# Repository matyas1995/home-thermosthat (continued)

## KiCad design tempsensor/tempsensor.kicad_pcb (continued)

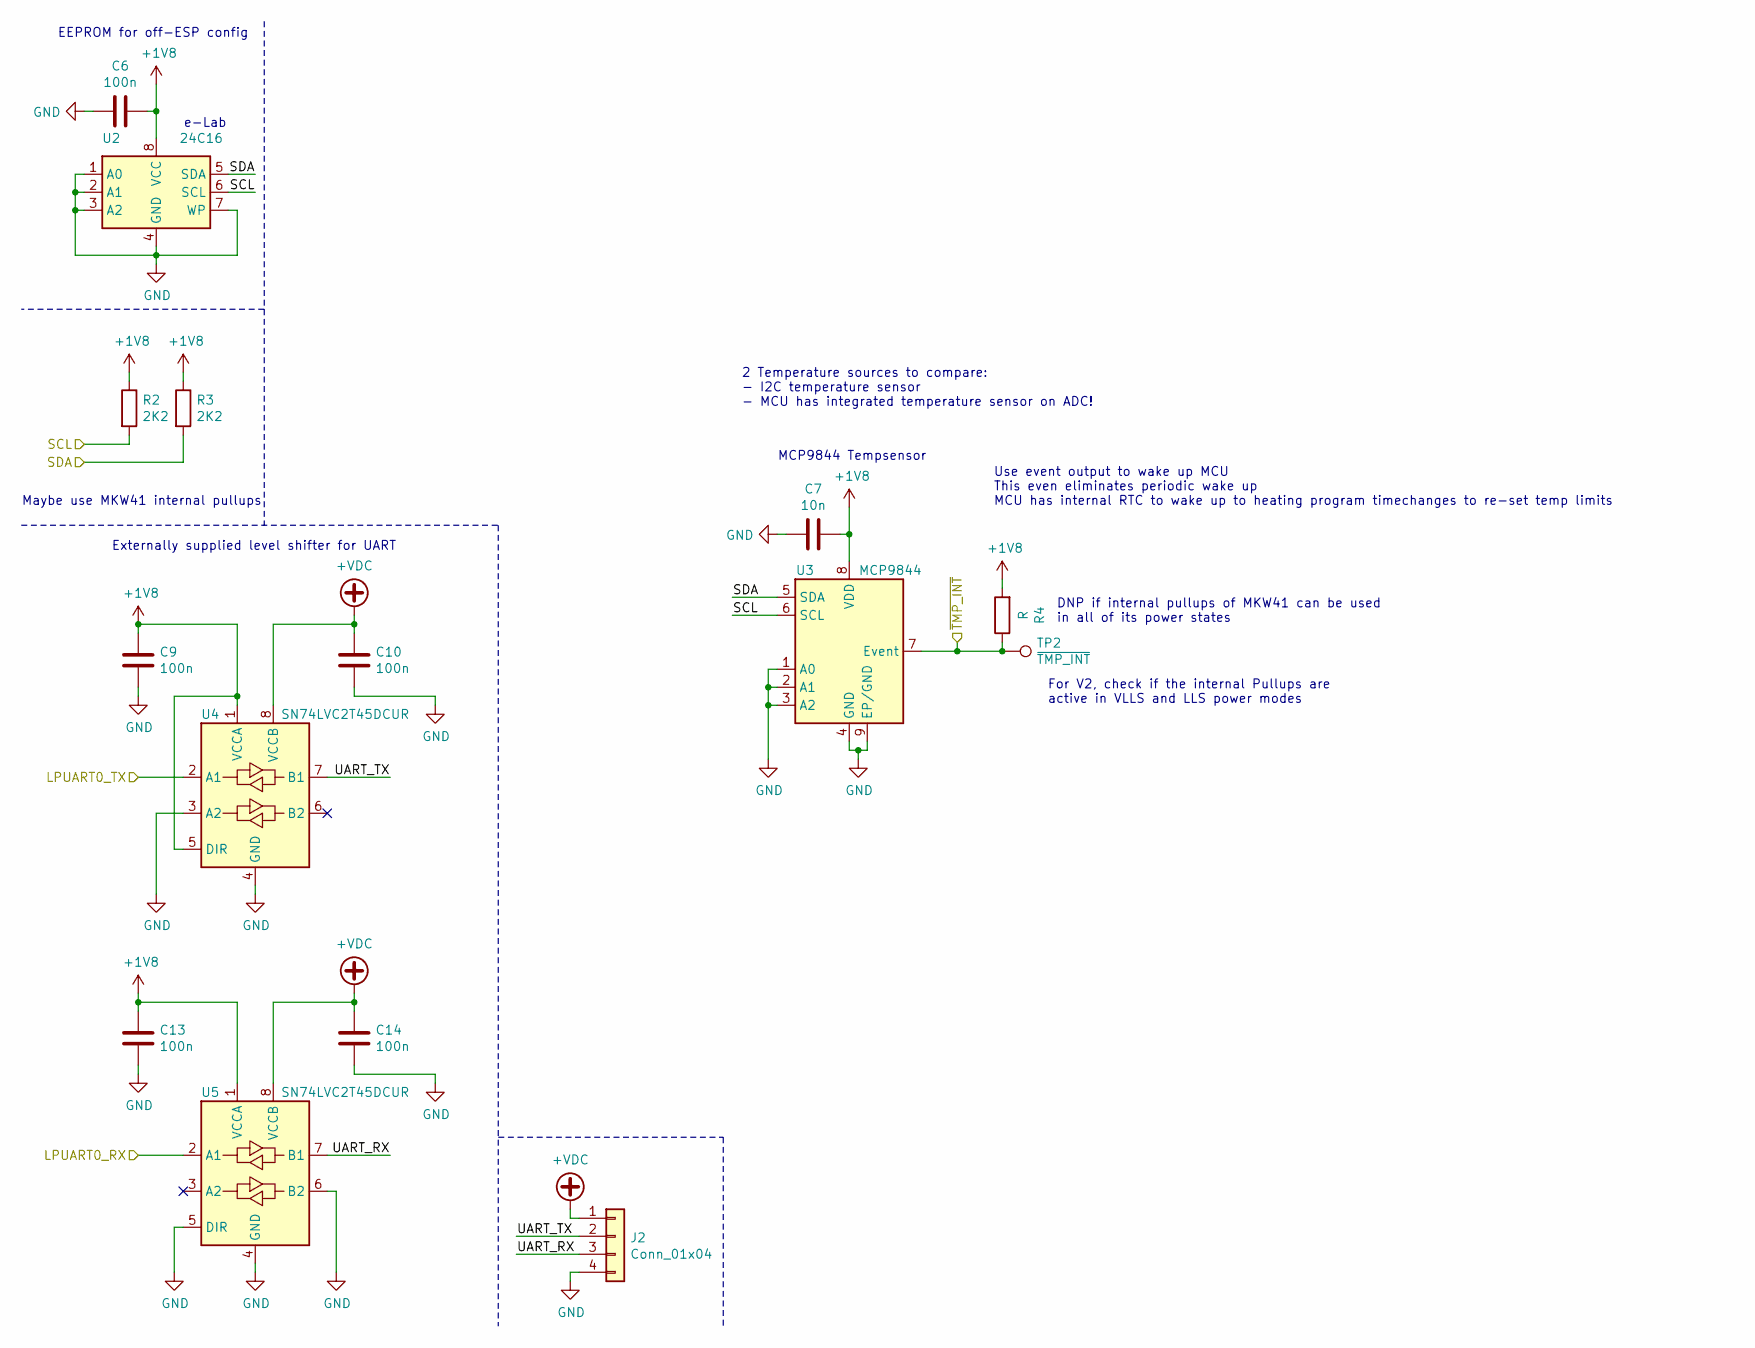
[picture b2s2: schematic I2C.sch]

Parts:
C6: 100n; C_0603_1608Metric
C7: 10n; C_0603_1608Metric
C9, C10, C13, C14: 100n; C_0402_1005Metric
J2: Conn_01x04; PinHeader_2x02_P2.54mm_Vertical
R2, R3: 2K2; R_0603_1608Metric
R4: R; R_0402_1005Metric
TP2: ~TMP_INT; TestPoint_Pad_D1.0mm
U2: 24C16; SOIC-8_3.9x4.9mm_P1.27mm
U3: MCP9844; DFN-8-1EP_3x2mm_P0.5mm_EP1.36x1.46mm
U4, U5: SN74LVC2T45DCUR; VSSOP-8_2.4x2.1mm_P0.5mm

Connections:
+1V8: C6.1, C7.1, C9.1, C13.1, R2.1, R3.1, R4.2, U2.8 (VCC), U3.8 (VDD), U4.1 (VCCA), U4.5 (DIR), U5.1 (VCCA); also elsewhere on the board
+VDC: C10.1, C14.1, J2.1, U4.8 (VCCB), U5.8 (VCCB)
/I2C/UART_RX: J2.3, U5.7 (B1)
/I2C/UART_TX: J2.2, U4.7 (B1)
/LPUART0_RX: U5.2 (A1); also elsewhere on the board
/LPUART0_TX: U4.2 (A1); also elsewhere on the board
/SCL: R2.2, U2.6 (SCL), U3.6 (SCL); also elsewhere on the board
/SDA: R3.2, U2.5 (SDA), U3.5 (SDA); also elsewhere on the board
/~TMP_INT: R4.1, TP2.1, U3.7 (Event); also elsewhere on the board
GND: C6.2, C7.2, C9.2, C10.2, C13.2, C14.2, J2.4, U2.1 (A0), U2.2 (A1), U2.3 (A2), U2.4 (GND), U2.7 (WP), U3.1 (A0), U3.2 (A1), U3.3 (A2), U3.4 (GND), U3.9 (EP/GND), U4.3 (A2), U4.4 (GND), U5.4 (GND), U5.5 (DIR), U5.6 (B2); also elsewhere on the board

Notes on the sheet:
EEPROM for off-ESP config
e-Lab
MCP9844 Tempsensor
Use event output to wake up MCU This even eliminates periodic wake up MCU has internal RTC to wake up to heating program timechanges to re-set temp limits
DNP if internal pullups of MKW41 can be used in all of its power states
For V2, check if the internal Pullups are active in VLLS and LLS power modes
Externally supplied level shifter for UART
Maybe use MKW41 internal pullups
2 Temperature sources to compare: - I2C temperature sensor - MCU has integrated temperature sensor on ADC!

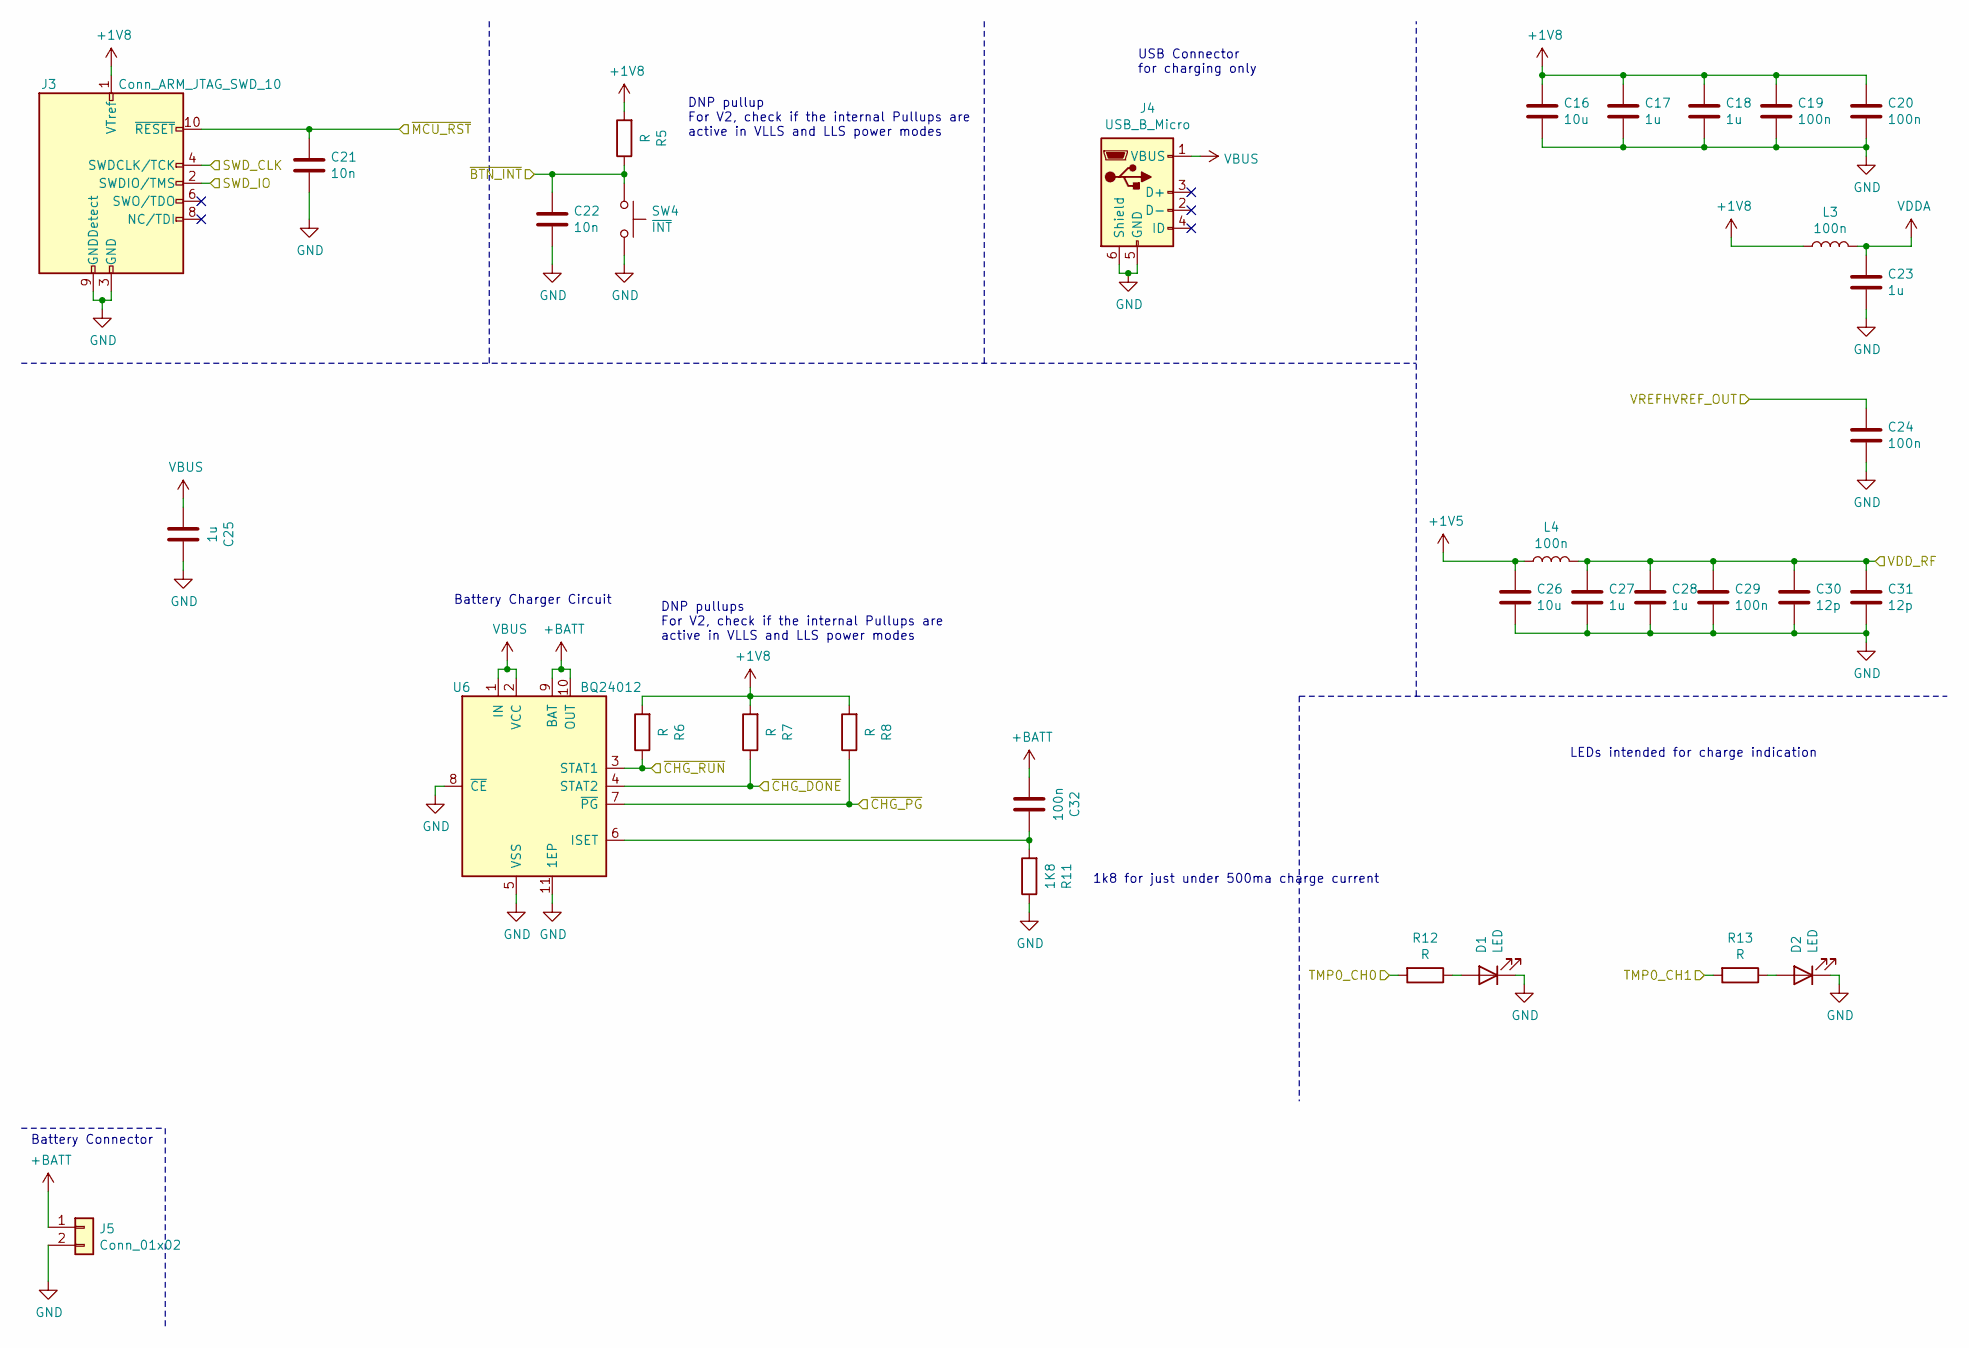
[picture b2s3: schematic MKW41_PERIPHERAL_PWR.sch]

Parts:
C16, C26: 10u; C_0603_1608Metric
C17, C18, C23, C27, C28: 1u; C_0402_1005Metric
C19, C20, C24, C29, C32: 100n; C_0402_1005Metric
C21, C22: 10n; C_0402_1005Metric
C25: 1u; C_0603_1608Metric
C30, C31: 12p; C_0402_1005Metric
D1, D2: LED; LED_0603_1608Metric
J3: Conn_ARM_JTAG_SWD_10; PinHeader_2x05_P1.27mm_Vertical_SMD
J4: USB_B_Micro; USB-Mini-B_Wuerth_651005136521_Horizontal
J5: Conn_01x02; PinHeader_1x02_P2.54mm_Vertical
L3, L4: 100n; L_0402_1005Metric
R5, R12, R13: R; R_0603_1608Metric
R6, R7, R8: R; R_0402_1005Metric
R11: 1K8; R_0402_1005Metric
SW4: ~INT; SW_PUSH_6mm_H5mm
U6: BQ24012; VSON-10-1EP_3x3mm_P0.5mm_EP1.65x2.4mm_ThermalVias

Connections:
+1V5: C26.1, L4.1; also elsewhere on the board
+1V8: C16.1, C17.1, C18.1, C19.1, C20.1, J3.1 (VTref), L3.1, R5.2, R6.2, R7.2, R8.2; also elsewhere on the board
+BATT: C32.2, J5.1, U6.9 (BAT), U6.10 (OUT); also elsewhere on the board
/SWD_CLK: J3.4 (SWDCLK/TCK); also elsewhere on the board
/SWD_IO: J3.2 (SWDIO/TMS); also elsewhere on the board
/TMP0_CH0: R12.2; also elsewhere on the board
/TMP0_CH1: R13.2; also elsewhere on the board
/VDD_RF: C27.1, C28.1, C29.1, C30.1, C31.1, L4.2; also elsewhere on the board
/VREFHVREF_OUT: C24.1; also elsewhere on the board
/~BTN_INT: C22.1, R5.1, SW4.1; also elsewhere on the board
/~CHG_DONE: R7.1, U6.4 (STAT2); also elsewhere on the board
/~CHG_PG: R8.1, U6.7 (~PG); also elsewhere on the board
/~CHG_RUN: R6.1, U6.3 (STAT1); also elsewhere on the board
/~MCU_RST: C21.1, J3.10 (~RESET~); also elsewhere on the board
GND: C16.2, C17.2, C18.2, C19.2, C20.2, C21.2, C22.2, C23.2, C24.2, C25.1, C26.2, C27.2, C28.2, C29.2, C30.2, C31.2, D1.1 (K), D2.1 (K), J3.3 (GND), J3.5 (GND), J3.9 (GNDDetect), J4.5 (GND), J4.6 (Shield), J5.2, R11.1, SW4.2, U6.5 (VSS), U6.8 (~CE), U6.11 (1EP); also elsewhere on the board
unnamed: C32.1, R11.2, U6.6 (ISET)
unnamed: D1.2 (A), R12.1
unnamed: D2.2 (A), R13.1
VBUS: C25.2, J4.1 (VBUS), U6.1 (IN), U6.2 (VCC)
VDDA: C23.1, L3.2; also elsewhere on the board

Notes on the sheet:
DNP pullup For V2, check if the internal Pullups are active in VLLS and LLS power modes
Battery Connector
Battery Charger Circuit
USB Connector for charging only
DNP pullups For V2, check if the internal Pullups are active in VLLS and LLS power modes
LEDs intended for charge indication
1k8 for just under 500ma charge current

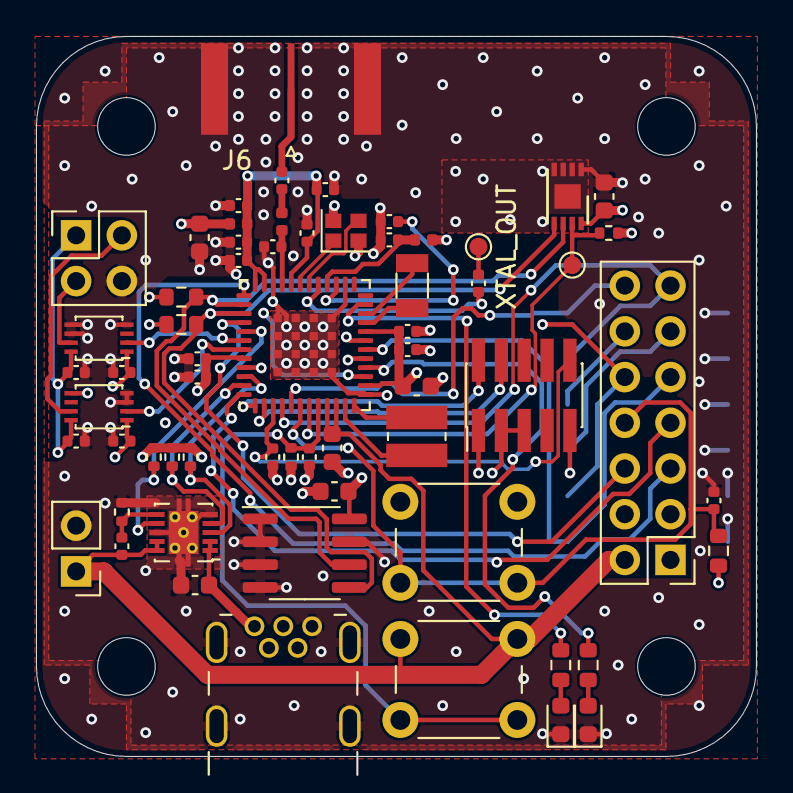
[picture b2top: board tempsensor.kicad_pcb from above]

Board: 4 copper layers, 40.0 x 40.0 mm, 64 parts (1 on the bottom side), 49 nets.

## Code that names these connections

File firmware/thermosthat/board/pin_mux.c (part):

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mcu_data: ksdk2_0
processor_version: 10.0.0
pin_labels:
- {pin_num: '16', pin_signal: PTB0/LLWU_P8/XTAL_OUT_EN/I2C0_SCL/CMP0_OUT/TPM0_CH1/CLKOUT, label: LED_YELLOW, identifier: LED_YELLOW}
- {pin_num: '17', pin_signal: ADC0_SE1/CMP0_IN5/PTB1/DTM_RX/I2C0_SDA/LPTMR0_ALT1/TPM0_CH2/CMT_IRO, label: LED_RED, identifier: LED_RED}
- {pin_num: '23', pin_signal: DAC0_OUT/ADC0_SE4/CMP0_IN2/PTB18/I2C1_SCL/TPM_CLKIN0/TPM0_CH0/NMI_b, label: REG_OUT, identifier: REG_OUT}
- {pin_num: '41', pin_signal: TSI0_CH1/PTC5/LLWU_P13/RF_NOT_ALLOWED/LPTMR0_ALT2/UART0_RTS_b/TPM1_CH1/BSM_CLK, label: BTN_INT, identifier: BTN_INT}
- {pin_num: '45', pin_signal: TSI0_CH4/PTC16/LLWU_P0/SPI0_SCK/I2C0_SDA/UART0_RTS_b/TPM0_CH3, label: LED_GREEN, identifier: LED_GREEN}
- {pin_num: '46', pin_signal: TSI0_CH5/PTC17/LLWU_P1/SPI0_SOUT/I2C1_SCL/UART0_RX/BSM_FRAME/DTM_RX, label: BTN_OK, identifier: BTN_OK}
- {pin_num: '47', pin_signal: TSI0_CH6/PTC18/LLWU_P2/SPI0_SIN/I2C1_SDA/UART0_TX/BSM_DATA/DTM_TX, label: DP_RST, identifier: DP_RST}
- {pin_num: '48', pin_signal: TSI0_CH7/PTC19/LLWU_P3/SPI0_PCS0/I2C0_SCL/UART0_CTS_b/BSM_CLK/BLE_RF_ACTIVE, label: DP_BUSY, identifier: DP_BUSY}
 * BE CAREFUL MODIFYING THIS COMMENT - IT IS YAML SETTINGS FOR TOOLS ***********
 */
/* clang-format on */
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BOARD_InitPins:
- options: {callFromInitBoot: 'true', coreID: core0, enableClock: 'true'}
- pin_list:
  - {pin_num: '4', peripheral: SPI1, signal: SOUT, pin_signal: TSI0_CH10/PTA16/LLWU_P4/SPI1_SOUT/TPM0_CH0}
  - {pin_num: '6', peripheral: SPI1, signal: SCK, pin_signal: TSI0_CH12/PTA18/LLWU_P6/SPI1_SCK/TPM2_CH0}
  - {pin_num: '7', peripheral: SPI1, signal: PCS0_SS, pin_signal: TSI0_CH13/ADC0_SE5/PTA19/LLWU_P7/SPI1_PCS0/TPM2_CH1}
  - {pin_num: '16', peripheral: GPIOB, signal: 'GPIO, 0', pin_signal: PTB0/LLWU_P8/XTAL_OUT_EN/I2C0_SCL/CMP0_OUT/TPM0_CH1/CLKOUT, direction: OUTPUT}
  - {pin_num: '17', peripheral: GPIOB, signal: 'GPIO, 1', pin_signal: ADC0_SE1/CMP0_IN5/PTB1/DTM_RX/I2C0_SDA/LPTMR0_ALT1/TPM0_CH2/CMT_IRO, direction: OUTPUT}
  - {pin_num: '21', peripheral: RTC, signal: EXTAL32K, pin_signal: EXTAL32K/PTB16/I2C1_SCL/TPM2_CH0}
  - {pin_num: '22', peripheral: RTC, signal: XTAL32K, pin_signal: XTAL32K/PTB17/I2C1_SDA/TPM2_CH1/BSM_CLK}
  - {pin_num: '23', peripheral: GPIOB, signal: 'GPIO, 18', pin_signal: DAC0_OUT/ADC0_SE4/CMP0_IN2/PTB18/I2C1_SCL/TPM_CLKIN0/TPM0_CH0/NMI_b, direction: OUTPUT}
  - {pin_num: '38', peripheral: I2C1, signal: CLK, pin_signal: TSI0_CH14/PTC2/LLWU_P10/TX_SWITCH/I2C1_SCL/UART0_RX/CMT_IRO/DTM_RX}
  - {pin_num: '39', peripheral: I2C1, signal: SDA, pin_signal: TSI0_CH15/PTC3/LLWU_P11/RX_SWITCH/I2C1_SDA/UART0_TX/TPM0_CH1/DTM_TX}
  - {pin_num: '41', peripheral: GPIOC, signal: 'GPIO, 5', pin_signal: TSI0_CH1/PTC5/LLWU_P13/RF_NOT_ALLOWED/LPTMR0_ALT2/UART0_RTS_b/TPM1_CH1/BSM_CLK, direction: INPUT}
  - {pin_num: '45', peripheral: GPIOC, signal: 'GPIO, 16', pin_signal: TSI0_CH4/PTC16/LLWU_P0/SPI0_SCK/I2C0_SDA/UART0_RTS_b/TPM0_CH3, direction: OUTPUT, gpio_init_state: 'true'}
  - {pin_num: '46', peripheral: GPIOC, signal: 'GPIO, 17', pin_signal: TSI0_CH5/PTC17/LLWU_P1/SPI0_SOUT/I2C1_SCL/UART0_RX/BSM_FRAME/DTM_RX, direction: INPUT}
  - {pin_num: '47', peripheral: GPIOC, signal: 'GPIO, 18', pin_signal: TSI0_CH6/PTC18/LLWU_P2/SPI0_SIN/I2C1_SDA/UART0_TX/BSM_DATA/DTM_TX, direction: OUTPUT}
  - {pin_num: '48', peripheral: GPIOC, signal: 'GPIO, 19', pin_signal: TSI0_CH7/PTC19/LLWU_P3/SPI0_PCS0/I2C0_SCL/UART0_CTS_b/BSM_CLK/BLE_RF_ACTIVE, direction: INPUT}
  - {pin_num: '43', peripheral: LPUART0, signal: TX, pin_signal: TSI0_CH3/PTC7/LLWU_P15/SPI0_PCS2/I2C1_SDA/UART0_TX/TPM2_CH1/BSM_DATA}
  - {pin_num: '42', peripheral: LPUART0, signal: RX, pin_signal: TSI0_CH2/PTC6/LLWU_P14/XTAL_OUT_EN/I2C1_SCL/UART0_RX/TPM2_CH0/BSM_FRAME}
 * BE CAREFUL MODIFYING THIS COMMENT - IT IS YAML SETTINGS FOR TOOLS ***********
 */
/* clang-format on */
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        .pinDirection = kGPIO_DigitalInput,
        .outputLogic = 0U
    };
    /* Initialize GPIO functionality on pin PTC19 (pin 48)  */
    GPIO_PinInit(BOARD_INITPINS_DP_BUSY_GPIO, BOARD_INITPINS_DP_BUSY_PIN, &DP_BUSY_config);

    /* PORTA16 (pin 4) is configured as SPI1_SOUT */
    PORT_SetPinMux(PORTA, 16U, kPORT_MuxAlt2);

    /* PORTA18 (pin 6) is configured as SPI1_SCK */
    PORT_SetPinMux(PORTA, 18U, kPORT_MuxAlt2);

    /* PORTA19 (pin 7) is configured as SPI1_PCS0 */
    PORT_SetPinMux(PORTA, 19U, kPORT_MuxAlt2);

    /* PORTB0 (pin 16) is configured as PTB0 */
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    /* PORTC18 (pin 47) is configured as PTC18 */
    PORT_SetPinMux(BOARD_INITPINS_DP_RST_PORT, BOARD_INITPINS_DP_RST_PIN, kPORT_MuxAsGpio);

    /* PORTC19 (pin 48) is configured as PTC19 */
    PORT_SetPinMux(BOARD_INITPINS_DP_BUSY_PORT, BOARD_INITPINS_DP_BUSY_PIN, kPORT_MuxAsGpio);

    /* PORTC2 (pin 38) is configured as I2C1_SCL */
    PORT_SetPinMux(PORTC, 2U, kPORT_MuxAlt3);

    /* PORTC3 (pin 39) is configured as I2C1_SDA */
    PORT_SetPinMux(PORTC, 3U, kPORT_MuxAlt3);

    /* PORTC5 (pin 41) is configured as PTC5 */
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                   /* Mask bits to zero which are setting */
                   (~(SIM_SOPT5_LPUART0TXSRC_MASK | SIM_SOPT5_LPUART0RXSRC_MASK)))

                  /* LPUART0 Transmit Data Source Select: LPUART0_TX pin. */
                  | SIM_SOPT5_LPUART0TXSRC(SOPT5_LPUART0TXSRC_LPUART_TX)

                  /* LPUART0 Receive Data Source Select: LPUART_RX pin. */
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
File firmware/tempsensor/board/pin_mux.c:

/***********************************************************************************************************************
 * This file was generated by the MCUXpresso Config Tools. Any manual edits made to this file
 * will be overwritten if the respective MCUXpresso Config Tools is used to update this file.
 **********************************************************************************************************************/

/* clang-format off */
/*
 * TEXT BELOW IS USED AS SETTING FOR TOOLS *************************************
!!GlobalInfo
product: Pins v10.0
processor: MKW41Z512xxx4
package_id: MKW41Z512VHT4
mcu_data: ksdk2_0
processor_version: 10.0.0
pin_labels:
- {pin_num: '6', pin_signal: TSI0_CH12/PTA18/LLWU_P6/SPI1_SCK/TPM2_CH0, label: BTN_INT, identifier: BTN_INT}
- {pin_num: '16', pin_signal: PTB0/LLWU_P8/XTAL_OUT_EN/I2C0_SCL/CMP0_OUT/TPM0_CH1/CLKOUT, label: LED_YELLOW, identifier: LED_YELLOW}
- {pin_num: '23', pin_signal: DAC0_OUT/ADC0_SE4/CMP0_IN2/PTB18/I2C1_SCL/TPM_CLKIN0/TPM0_CH0/NMI_b, label: LED_RED, identifier: LED_RED}
- {pin_num: '41', pin_signal: TSI0_CH1/PTC5/LLWU_P13/RF_NOT_ALLOWED/LPTMR0_ALT2/UART0_RTS_b/TPM1_CH1/BSM_CLK, label: CHG_PG, identifier: CHG_PG}
- {pin_num: '46', pin_signal: TSI0_CH5/PTC17/LLWU_P1/SPI0_SOUT/I2C1_SCL/UART0_RX/BSM_FRAME/DTM_RX, label: CHG_ROG, identifier: CHG_RUN}
- {pin_num: '47', pin_signal: TSI0_CH6/PTC18/LLWU_P2/SPI0_SIN/I2C1_SDA/UART0_TX/BSM_DATA/DTM_TX, label: CHG_DONE, identifier: CHG_DONE}
 * BE CAREFUL MODIFYING THIS COMMENT - IT IS YAML SETTINGS FOR TOOLS ***********
 */
/* clang-format on */

#include "fsl_common.h"
#include "fsl_port.h"
#include "fsl_gpio.h"
#include "pin_mux.h"

/* FUNCTION ************************************************************************************************************
 *
 * Function Name : BOARD_InitBootPins
 * Description   : Calls initialization functions.
 *
 * END ****************************************************************************************************************/
void BOARD_InitBootPins(void)
{
    BOARD_InitPins();
}

/* clang-format off */
/*
 * TEXT BELOW IS USED AS SETTING FOR TOOLS *************************************
BOARD_InitPins:
- options: {callFromInitBoot: 'true', coreID: core0, enableClock: 'true'}
- pin_list:
  - {pin_num: '6', peripheral: GPIOA, signal: 'GPIO, 18', pin_signal: TSI0_CH12/PTA18/LLWU_P6/SPI1_SCK/TPM2_CH0, direction: INPUT, gpio_interrupt: kPORT_InterruptFallingEdge}
  - {pin_num: '16', peripheral: GPIOB, signal: 'GPIO, 0', pin_signal: PTB0/LLWU_P8/XTAL_OUT_EN/I2C0_SCL/CMP0_OUT/TPM0_CH1/CLKOUT, direction: OUTPUT}
  - {pin_num: '23', peripheral: GPIOB, signal: 'GPIO, 18', pin_signal: DAC0_OUT/ADC0_SE4/CMP0_IN2/PTB18/I2C1_SCL/TPM_CLKIN0/TPM0_CH0/NMI_b, direction: OUTPUT}
  - {pin_num: '41', peripheral: GPIOC, signal: 'GPIO, 5', pin_signal: TSI0_CH1/PTC5/LLWU_P13/RF_NOT_ALLOWED/LPTMR0_ALT2/UART0_RTS_b/TPM1_CH1/BSM_CLK, direction: INPUT,
    gpio_interrupt: kPORT_InterruptEitherEdge}
  - {pin_num: '46', peripheral: GPIOC, signal: 'GPIO, 17', pin_signal: TSI0_CH5/PTC17/LLWU_P1/SPI0_SOUT/I2C1_SCL/UART0_RX/BSM_FRAME/DTM_RX, direction: INPUT, gpio_interrupt: kPORT_InterruptEitherEdge}
  - {pin_num: '47', peripheral: GPIOC, signal: 'GPIO, 18', pin_signal: TSI0_CH6/PTC18/LLWU_P2/SPI0_SIN/I2C1_SDA/UART0_TX/BSM_DATA/DTM_TX, direction: INPUT, gpio_interrupt: kPORT_InterruptEitherEdge}
  - {pin_num: '38', peripheral: I2C1, signal: CLK, pin_signal: TSI0_CH14/PTC2/LLWU_P10/TX_SWITCH/I2C1_SCL/UART0_RX/CMT_IRO/DTM_RX}
  - {pin_num: '39', peripheral: I2C1, signal: SDA, pin_signal: TSI0_CH15/PTC3/LLWU_P11/RX_SWITCH/I2C1_SDA/UART0_TX/TPM0_CH1/DTM_TX}
 * BE CAREFUL MODIFYING THIS COMMENT - IT IS YAML SETTINGS FOR TOOLS ***********
 */
/* clang-format on */

/* FUNCTION ************************************************************************************************************
 *
 * Function Name : BOARD_InitPins
 * Description   : Configures pin routing and optionally pin electrical features.
 *
 * END ****************************************************************************************************************/
void BOARD_InitPins(void)
{
    /* Port A Clock Gate Control: Clock enabled */
    CLOCK_EnableClock(kCLOCK_PortA);
    /* Port B Clock Gate Control: Clock enabled */
    CLOCK_EnableClock(kCLOCK_PortB);
    /* Port C Clock Gate Control: Clock enabled */
    CLOCK_EnableClock(kCLOCK_PortC);

    gpio_pin_config_t BTN_INT_config = {
        .pinDirection = kGPIO_DigitalInput,
        .outputLogic = 0U
    };
    /* Initialize GPIO functionality on pin PTA18 (pin 6)  */
    GPIO_PinInit(BOARD_INITPINS_BTN_INT_GPIO, BOARD_INITPINS_BTN_INT_PIN, &BTN_INT_config);

    gpio_pin_config_t LED_YELLOW_config = {
        .pinDirection = kGPIO_DigitalOutput,
        .outputLogic = 0U
    };
    /* Initialize GPIO functionality on pin PTB0 (pin 16)  */
    GPIO_PinInit(BOARD_INITPINS_LED_YELLOW_GPIO, BOARD_INITPINS_LED_YELLOW_PIN, &LED_YELLOW_config);

    gpio_pin_config_t LED_RED_config = {
        .pinDirection = kGPIO_DigitalOutput,
        .outputLogic = 0U
    };
    /* Initialize GPIO functionality on pin PTB18 (pin 23)  */
    GPIO_PinInit(BOARD_INITPINS_LED_RED_GPIO, BOARD_INITPINS_LED_RED_PIN, &LED_RED_config);

    gpio_pin_config_t CHG_PG_config = {
        .pinDirection = kGPIO_DigitalInput,
        .outputLogic = 0U
    };
    /* Initialize GPIO functionality on pin PTC5 (pin 41)  */
    GPIO_PinInit(BOARD_INITPINS_CHG_PG_GPIO, BOARD_INITPINS_CHG_PG_PIN, &CHG_PG_config);

    gpio_pin_config_t CHG_RUN_config = {
        .pinDirection = kGPIO_DigitalInput,
        .outputLogic = 0U
    };
    /* Initialize GPIO functionality on pin PTC17 (pin 46)  */
    GPIO_PinInit(BOARD_INITPINS_CHG_RUN_GPIO, BOARD_INITPINS_CHG_RUN_PIN, &CHG_RUN_config);

    gpio_pin_config_t CHG_DONE_config = {
        .pinDirection = kGPIO_DigitalInput,
        .outputLogic = 0U
    };
    /* Initialize GPIO functionality on pin PTC18 (pin 47)  */
    GPIO_PinInit(BOARD_INITPINS_CHG_DONE_GPIO, BOARD_INITPINS_CHG_DONE_PIN, &CHG_DONE_config);

    /* PORTA18 (pin 6) is configured as PTA18 */
    PORT_SetPinMux(BOARD_INITPINS_BTN_INT_PORT, BOARD_INITPINS_BTN_INT_PIN, kPORT_MuxAsGpio);

    /* Interrupt configuration on PORTA18 (pin 6): Interrupt on falling edge */
    PORT_SetPinInterruptConfig(BOARD_INITPINS_BTN_INT_PORT, BOARD_INITPINS_BTN_INT_PIN, kPORT_InterruptFallingEdge);

    /* PORTB0 (pin 16) is configured as PTB0 */
    PORT_SetPinMux(BOARD_INITPINS_LED_YELLOW_PORT, BOARD_INITPINS_LED_YELLOW_PIN, kPORT_MuxAsGpio);

    /* PORTB18 (pin 23) is configured as PTB18 */
    PORT_SetPinMux(BOARD_INITPINS_LED_RED_PORT, BOARD_INITPINS_LED_RED_PIN, kPORT_MuxAsGpio);

    /* PORTC17 (pin 46) is configured as PTC17 */
    PORT_SetPinMux(BOARD_INITPINS_CHG_RUN_PORT, BOARD_INITPINS_CHG_RUN_PIN, kPORT_MuxAsGpio);

    /* Interrupt configuration on PORTC17 (pin 46): Interrupt on either edge */
    PORT_SetPinInterruptConfig(BOARD_INITPINS_CHG_RUN_PORT, BOARD_INITPINS_CHG_RUN_PIN, kPORT_InterruptEitherEdge);

    /* PORTC18 (pin 47) is configured as PTC18 */
    PORT_SetPinMux(BOARD_INITPINS_CHG_DONE_PORT, BOARD_INITPINS_CHG_DONE_PIN, kPORT_MuxAsGpio);

    /* Interrupt configuration on PORTC18 (pin 47): Interrupt on either edge */
    PORT_SetPinInterruptConfig(BOARD_INITPINS_CHG_DONE_PORT, BOARD_INITPINS_CHG_DONE_PIN, kPORT_InterruptEitherEdge);

    /* PORTC2 (pin 38) is configured as I2C1_SCL */
    PORT_SetPinMux(PORTC, 2U, kPORT_MuxAlt3);

    /* PORTC3 (pin 39) is configured as I2C1_SDA */
    PORT_SetPinMux(PORTC, 3U, kPORT_MuxAlt3);

    /* PORTC5 (pin 41) is configured as PTC5 */
    PORT_SetPinMux(BOARD_INITPINS_CHG_PG_PORT, BOARD_INITPINS_CHG_PG_PIN, kPORT_MuxAsGpio);

    /* Interrupt configuration on PORTC5 (pin 41): Interrupt on either edge */
    PORT_SetPinInterruptConfig(BOARD_INITPINS_CHG_PG_PORT, BOARD_INITPINS_CHG_PG_PIN, kPORT_InterruptEitherEdge);
}
/***********************************************************************************************************************
 * EOF
 **********************************************************************************************************************/

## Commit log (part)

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2020-02-29 Started work on thermostat, power converters and buttons still missing from schematic.
2020-03-03 Added power supply and thermosthat control circuitry.
2020-03-03 Added RTC for timekeeping, AVR can now measure supply voltage.
2020-03-03 Changed usb port to ISP programming as CP2102 IC is not available from Reichelt.
2020-03-03 Added Temperature sensor.
2020-03-04 Exchanged 3,3V LDO with one I found at home.
2020-03-05 Exchanged AVR crystal with one I already have.
2020-03-05 Started adding footprints.
2020-03-05 Added footprints to most symbols.
2020-03-13 Moved project files for thermostat into subdirectory to make space for the other hardware files.
2020-03-13 Exchnged cached MCP9844 tempsensor with merged one from upstream.
2020-03-13 Created first rough draft of the temperature sensors.
2020-03-13 Added testpads to tempsensor, added missing TWI lines to EEPROM.
2020-03-13 Removed OP-AMP from tempsensor, not really needed.
2020-03-19 Added remaining footprints to thermosthat, redesigned self-turn-off circuit of tempsensor.
2020-03-19 Started working on thermosthat PCB, just assorting footprints by function group.
2020-03-27 Started layouting thermosthat.
2020-03-27 Advanced component placement, laid out some routes.
2020-03-29 Finished layout of Thermosthat.
2020-03-29 Added interrupt circuit to tempsensor MCP9844 to allow it to wake up ESP on temperature changes (so that I can program thresholds instead of waking up more often).
2020-03-29 Added some footprints to tempsensor.
2020-03-30 Tempsensor finished adding footprints
2020-03-30 Created 4x4cm PCB for tempsensor, first routing done.
2020-05-03 Commit cache to save library parts.
2020-07-29 Removed ESP from schematic, will switch over to NXP MKW41Z as it has better documentation, easier peripherals and support for low power thread protocol instead of WLAN to save energy in battery backe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
2020-08-08 Moved eINK display circuit into its own schematic to abstract control signals. Added a document about touch sensing. Touch should not be implemented on this revision.
2020-08-08 Moved RTC chip and temperature sensor to separate schematic for better organisation. No interrupt from RTC chip is used as the MKW41Z has its own RTC with interrupt function and only needs the RTC ch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
2020-08-10 Finished minimal connections for MKW41Z (I hope), added design files for FRDM development board to look up antenna connections etc.
2020-08-10 Added manual reset button to schematic. Might come handy sometime.
2020-08-10 Removed 0Ohm capacitor from 32,768KHz crystal as it was only for bypassing crystal in evalboard if the MCU pin is used otherwise.
2020-08-10 Added some helpful comments to schematic, added explanation document to schematic of evalboard.
2020-08-11 Added some comments to pin usage on MKW41Z, reconfigured display to use 3 line SPI (no Data/Command pin) with 9 bit data packets
2020-08-11 Added some descriptions and the possibility to use VDD as reference voltage for the ADC of the MKW41Z. This can come handy if we want to use the ADC to measure voltages.
2020-08-11 Deleted ATMega from schematics because I will only use the MKW41Z for everything.
2020-08-11 Moved I2C peripherals into one schematic, moved GPIO peripherals onto main schematic.
2020-08-16 Put LEDs and GPIOs into separate schematic, GPIO for arrow buttons are now attached over an expander.
2020-09-20 Updated symbols after library update, some footprints still need to be assigned. Deleted PCB except for Display and buttons. Button arrangement wrong. Move buttons to other side of Display. Maybe put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
2020-09-25 Finalized Thermostat circuit based on the MKW41Z.
2020-09-25 Added testpad to supply rail +5V to allow flexible powering of board,also over Arduino.
2020-09-26 Started grouping footprints on PCB, configured minimal via and trace sizes for PCB_POOL.
2020-09-26 Started routing some subgroups, going to put GPIO on other board and not attach display directly, as that would make the PCB too large and expensive.
2020-09-28 Fine grouping of parts done, may start routing . GPIO connector on wrong side of PCB (I wanted to have the buttons on the opposite side, but thats not a big problem.
2020-09-29 Changed LED and regulator_out drivers to NMOS instead of bipolar. Started routing, SPI and I2C lines done.
2020-10-01 Modivied DRC constraints according to specs of PCB_POOL, finished layouting signal lines, only power is left.
2020-10-05 Finished routing except for the RF line, still need to add many many grounding vias.
2020-10-10 Continued deleting unnecessary vias overlapping with traces and footprints.
2020-10-10 Created GND plane stitching with helper script, added markings to pin headers, solder jumpers and pin1 of footprints. Ready for manufacturing.
2020-10-10 Changed footprint of MKW41Z to one with individual center GND pads and no thermal vias so that I am able to set own via sizes for the thermals.
2020-10-13 Replaced DCDC input cap as the package was way too small for the required capacitance, started working on the BOM and looking up parts on Mouser. Need to replace input Molex connector as it is not in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
2020-10-15 Replaced Molex PicoBlade SMT connector with THT version as this is available at Mouser. This also helps since the pins act as vias. Resolved DRC errors, Antenna trace needs to be set then we are read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
2020-10-26 Created base schematic for MKW41 tempsensor, still need to finetune it.
2020-11-03 Finished Tempsensor schematic based on MKW41Z. Many footprints not associated yet.
2020-11-03 Added footprints to tempsensor.
2020-11-16 Started layouting the TempSensor, exchanged the large LEDs for 0603 LEDs (from ELAB). MCU needs to be placed. Changed signals on expansion header to put power pins onto just one end.
2020-12-08 Finished layouting tempsensor and thermostat. Parts are ordered from Mouser, PCB ordered from beta-layout.
2020-12-13 Specified some resistor values.
2020-12-23 Changed UART level shifter package on thermosthat, however there is not enough space on tempsensor.
2021-03-18 Initial commit for firmware, created skeleton MCUXpresso project for tempsensor.
2021-04-07 Extended skeleton project with a basic board initialization and a basic task that periodically reads the battery voltage.
2021-04-18 Created register makros for MCP9844 registers. Started developing RTOS peripheral drivers as their own tasks that communicate over queues. This may not be perfect as using mutexes would allow for pri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
2021-05-02 Changed ADC driver back to use functions and mutexes. No RTOS task apart from main may call init and deinit function.
2021-05-02 Created little task to initialize I2C and to read out the tempsensor(s). Utterly needs calibration.
2021-05-16 Moved part names and values back from fab layer to silkscreen layer. Otherwise, printing placement plans is very confusing.
2021-06-02 Resolved merge conflicts upon retrieving stashed stuff.
2021-06-10 Added skeleton project for thermosthat firmware.
2021-06-10 Configured MCU pins (without interrupts).
2021-06-10 Removed pulldown resistor on regulator out pin of MCU. This pin is default non-maskable interrupt pin. On reset, this pulldown resistor immediately triggered the NMI interrupt, sabotaging the startup.
2021-10-29 Copied sources over from OpenThread official port back to MCUXpresso IDE. Will not compile straigt away and need to change bits relating to FRDM evalboard (NMI handler etc.). Also not sure how and if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
2021-12-21 Configured LPUART clock over the MCUXpresso clock config tool.
2022-01-14 Added sources, includes and defines to C++ compiler, included remaining fsl drivers so that compilation now runs without errors. The linker still throws major hassle as the image is 20 percent bigger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
2022-01-16 Turned on compile optimization and link against NewLib(Nano) with nohost option. This actually yields a result that fits into device flash. Not testet for functionality though.
2022-01-30 Managed to integrate openthread and kw41z port into MCUEclipse so that there are no compilation errors or warnings. System init fails to complete though due to CAlloc of openthread failing to allocat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
2022-02-13 OpenThread finally starts with FreeRTOS. OpenThread process not interrupt driven (yet). UART will need to get its own process for that. Did not try to create wireless network yet, only CLI app seems 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
2022-02-18 Added MCUXpresso project file (nothing much changed probably, just a save commit)
2022-02-18 Pulled SDK code out of the MCUXpresso thermosthat project up into the firmware folder. This is to both allow the thermosthat and tempsensor to share SDK code and to reduce code redundancy before star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
2022-02-21 Changed openthread port config file to define uart lock header as a file instead of a fixed include (that way it was included everywhere).
2022-02-22 Started to modify the firmware project folder structure to use Cmake as the build system. This is to ultimately part with MCUXpresso and use Kdevelop or something else as an editor. The MCUXpresso pr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
2022-02-25 Moving forward to compile project with Cmake. Discovered that Openthread did not use the FreeRTOS memory calloc functions (I thought I implemented that one already...). So that still needs to be done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
2022-02-27 Added the linker script from OpenThread authors. Does not work yet, something is missing. Also changed FreeRTOS config to use a pre-defined array as heap and put this array at the adress where the li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
2022-03-07 Completed CMakeLists files so that the thermoshat firmware compiles and links. Did not flash and tested it though.
2022-03-07 Removed MCUXpresso project files from thermosthat folder.
2022-03-07 Cannot do without an stdlib because so much depends on memset and memcpy. Also deleted some more remnants of MCUXpressoIDE. Added a Readme and ToDo for the software folder.
2022-03-10 Added readme files and bash script to bootstrap cmake project for build.
2022-03-10 Modified CMakeLists.txt minimum required version. Added GCC optimization flag for size to compiler defaults.
2022-03-10 Renamed thermosthat firmware file with .elf ending to make its purpose more clear. Also added the --print-memory-usage linker flag to output the binary stats after building. Its important to know if 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
2022-03-13 Added -g option to COMPILER_FLAGS to embed symbol references into the image. This allows to set breakpoints by specifying the source file and line number.
2022-03-13 Added KDevelop project file(s). This is only for KDevelop to correctly set up the debug view. Not like Eclipse, building still happens with Cmake.
2022-03-13 Modified debugger script to automatically add a breakpoint at main() and start CPU.
2022-03-13 Removed -g flag from compiler COMMON_C_FLAGS. This will either have to be set by user on the command line or is configured in KDevelop debug launch.
2022-03-13 Added assembler init code as this maybe does better than the crappy c code. Compile does not work as Cmake somewhere adds a -x c flag, forcing the assembler file to go through GCC as if it was C. Som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
2022-04-12 Figured out how to get the project to build with Cmake 3.22 following advice from a ticket I created at Cmake gitlab
2022-08-11 Extended todo and readme for more clarity, added build script to easily start builds from the console. Build script directs make to use 16 threads.
2022-08-11 Added some points to todo
2022-08-12 Created little script to automatically send patch emails to me, in case I am developing somewhere without access to my gitserver and am not on the laptop to carry home for a git push
2022-08-12 Modified patch emailer script to automatically email all new commits on the current branch since the origin/BRANCH state.
2022-08-12 End of test commits
2022-08-15 Created debug flag variables for CMAKE to be able to determine compiler flags by setting CMAKE_BUILD_TYPE
2022-08-27 Managed to put FreeRTOS heap to right address by adding its name to the linker script.
